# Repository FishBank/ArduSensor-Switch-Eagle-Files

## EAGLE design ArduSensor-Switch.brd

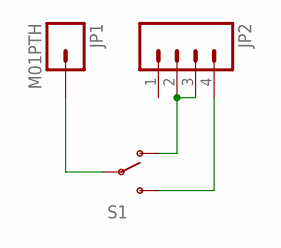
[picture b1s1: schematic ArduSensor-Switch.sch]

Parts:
JP1: M01PTH; 1X01
JP2: M04PTH; 1X04
S1: SWITCH-SPDTPTH; SWITCH-SPDT

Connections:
unnamed: JP2.2, JP2.3, S1.1 (O)
unnamed: JP1.1, S1.2
unnamed: JP2.4, S1.3 (S)

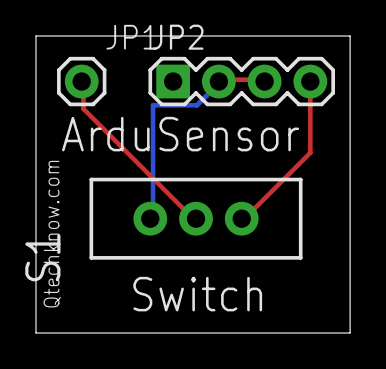
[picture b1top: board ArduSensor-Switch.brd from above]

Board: 2 copper layers, 17.4 x 16.5 mm, 3 parts (0 on the bottom side), 3 nets.

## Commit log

2012-07-13 Schematic

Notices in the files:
parts and their libraries:
SFE Connectors: Licensing: CC v3.0 Share-Alike You are welcome to use this library for commercial purposes.
